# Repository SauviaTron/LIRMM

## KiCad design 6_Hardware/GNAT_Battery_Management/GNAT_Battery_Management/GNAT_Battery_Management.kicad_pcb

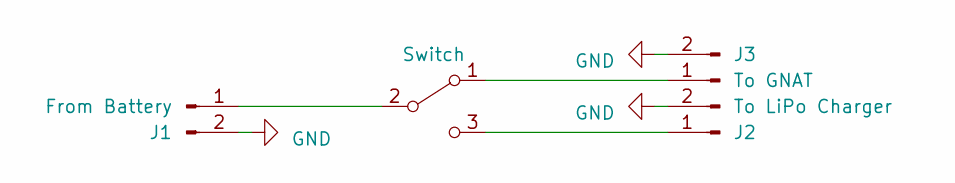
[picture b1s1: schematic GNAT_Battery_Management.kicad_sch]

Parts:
J1: From Battery; Battery_Connector
J2: To LiPo Charger; PinHeader_1x02_P2.54mm_Horizontal
J3: To GNAT; Holes_2x1
SW1: Switch; SW_PCM12SMTR

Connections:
GND: J1.2, J2.2, J3.2
unnamed: J1.1, SW1.2 (B)
unnamed: J2.1, SW1.3 (C)
unnamed: J3.1, SW1.1 (A)

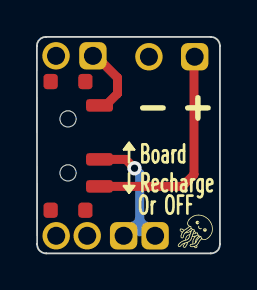
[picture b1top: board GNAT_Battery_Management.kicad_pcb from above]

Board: 2 copper layers, 10.2 x 12.0 mm, 4 parts (0 on the bottom side), 4 nets.

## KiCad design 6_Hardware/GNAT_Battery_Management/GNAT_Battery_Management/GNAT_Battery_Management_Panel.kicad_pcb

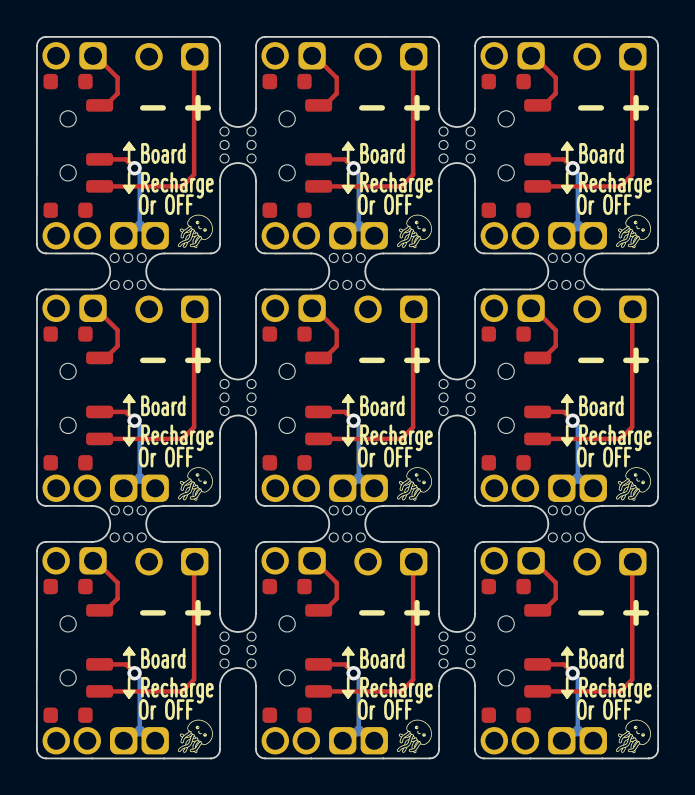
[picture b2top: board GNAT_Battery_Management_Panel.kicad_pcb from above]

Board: 2 copper layers, 34.5 x 40.1 mm, 48 parts (0 on the bottom side), 4 nets.

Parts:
J1, J4, J7, J10, J13, J16, J19, J22, J25: From Battery; Battery_Connector
J2, J5, J8, J11, J14, J17, J20, J23, J26: To LiPo Charger; PinHeader_1x02_P2.54mm_Horizontal
J3, J6, J9, J12, J15, J18, J21, J24, J27: To GNAT; Holes_2x1
SW1, SW2, SW3, SW4, SW5, SW6, SW7, SW8, SW9: Switch; SW_PCM12SMTR
mouse-bite-2mm-slot, mouse-bite-2mm-slot1, mouse-bite-2mm-slot2, mouse-bite-2mm-slot3, mouse-bite-2mm-slot5, mouse-bite-2mm-slot6, mouse-bite-2mm-slot7, mouse-bite-2mm-slot8, mouse-bite-2mm-slot9, mouse-bite-2mm-slot12, mouse-bite-2mm-slot14, mouse-bite-2mm-slot#2: VAL**; mouse-bite-2mm-slot

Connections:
GND: J1.2, J2.2, J3.2, J4.2, J5.2, J6.2, J7.2, J8.2, J9.2, J10.2, J11.2, J12.2, J13.2, J14.2, J15.2, J16.2, J17.2, J18.2, J19.2, J20.2, J21.2, J22.2, J23.2, J24.2, J25.2, J26.2, J27.2
unnamed: J1.1, J4.1, J7.1, J10.1, J13.1, J16.1, J19.1, J22.1, J25.1, SW1.2 (B), SW2.2 (B), SW3.2 (B), SW4.2 (B), SW5.2 (B), SW6.2 (B), SW7.2 (B), SW8.2 (B), SW9.2 (B)
unnamed: J2.1, J5.1, J8.1, J11.1, J14.1, J17.1, J20.1, J23.1, J26.1, SW1.3 (C), SW2.3 (C), SW3.3 (C), SW4.3 (C), SW5.3 (C), SW6.3 (C), SW7.3 (C), SW8.3 (C), SW9.3 (C)
unnamed: J3.1, J6.1, J9.1, J12.1, J15.1, J18.1, J21.1, J24.1, J27.1, SW1.1 (A), SW2.1 (A), SW3.1 (A), SW4.1 (A), SW5.1 (A), SW6.1 (A), SW7.1 (A), SW8.1 (A), SW9.1 (A)

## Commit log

2023-02-13 Add GPS
2023-02-13 RTC Congif for Rescue Mode
2023-02-13 RTC Config for Rescue Mode
2023-02-14 GPS add ReadUpdate and FirstFix fct
2023-02-14 RTC add custom Match for GPS debugging
2023-02-14 GPS - Periodic Fix with RTC
2023-02-14 Add .gitignore file
2023-02-15 Add LoRa communication
2023-02-15 Add Battery Monitoring
2023-02-15 LoRa - Send GPS Data W/ Better Precision + Delete Altitude
2023-02-15 LIS2DW12 - Put Features In .cpp and .h
2023-02-15 LIS2DW12 - Patch Constructor/Destructor
2023-02-16 I2C - Put Features In .cpp and .h files
2023-02-16 LoRa - Put Config And JoinOTAA in .cpp and .h files
2023-02-16 GPS - Add Features In .cpp and .h files
2023-02-16 Acc - Patch
2023-02-16 STM32 - Put Features In .cpp and .h files
2023-02-16 RTC - New Routing
2023-02-17 LIS2DW12 - Cleaning code
2023-02-17 Big Cleaning of the coms
2023-02-17 Adding files
2023-02-17 Patch
2023-02-17 Patch *.
2023-02-21 Add Directions
2023-02-21 Preform - Test @15°
2023-02-21 GPS - Cleaning code
2023-02-21 Flash - Add Features
2023-02-21 Flash - Patch Flash Address
2023-02-24 GPS - Add a Master Date Variable
2023-02-24 Cleaning Code
2023-02-24 Add STM32L0_Playground
2023-02-27 Add GPS Playground
2023-02-28 Add Acc Playground
2023-02-28 Power Measurement for STM32L0
2023-03-01 Flash R&W - Code cleaning
2023-03-01 JellyTracker - Power Tests
2023-03-03 LoraWAN Fixes
2023-03-30 Clean Code
2023-03-30 Create New Cayenne LPP
2023-03-30 Jellyfish Impulse Code Creation
2023-03-30 Cleaning Folder Direction
2023-04-11 Patch Battery Reading
2023-04-11 NRJ Study
2023-04-11 New Code For New Experiment
2023-07-31 Raw Data
2023-07-31 Preform file
2023-07-31 Photo
2023-07-31 STL files
2023-07-31 Other
2023-08-28 Cleaning Flash Section
